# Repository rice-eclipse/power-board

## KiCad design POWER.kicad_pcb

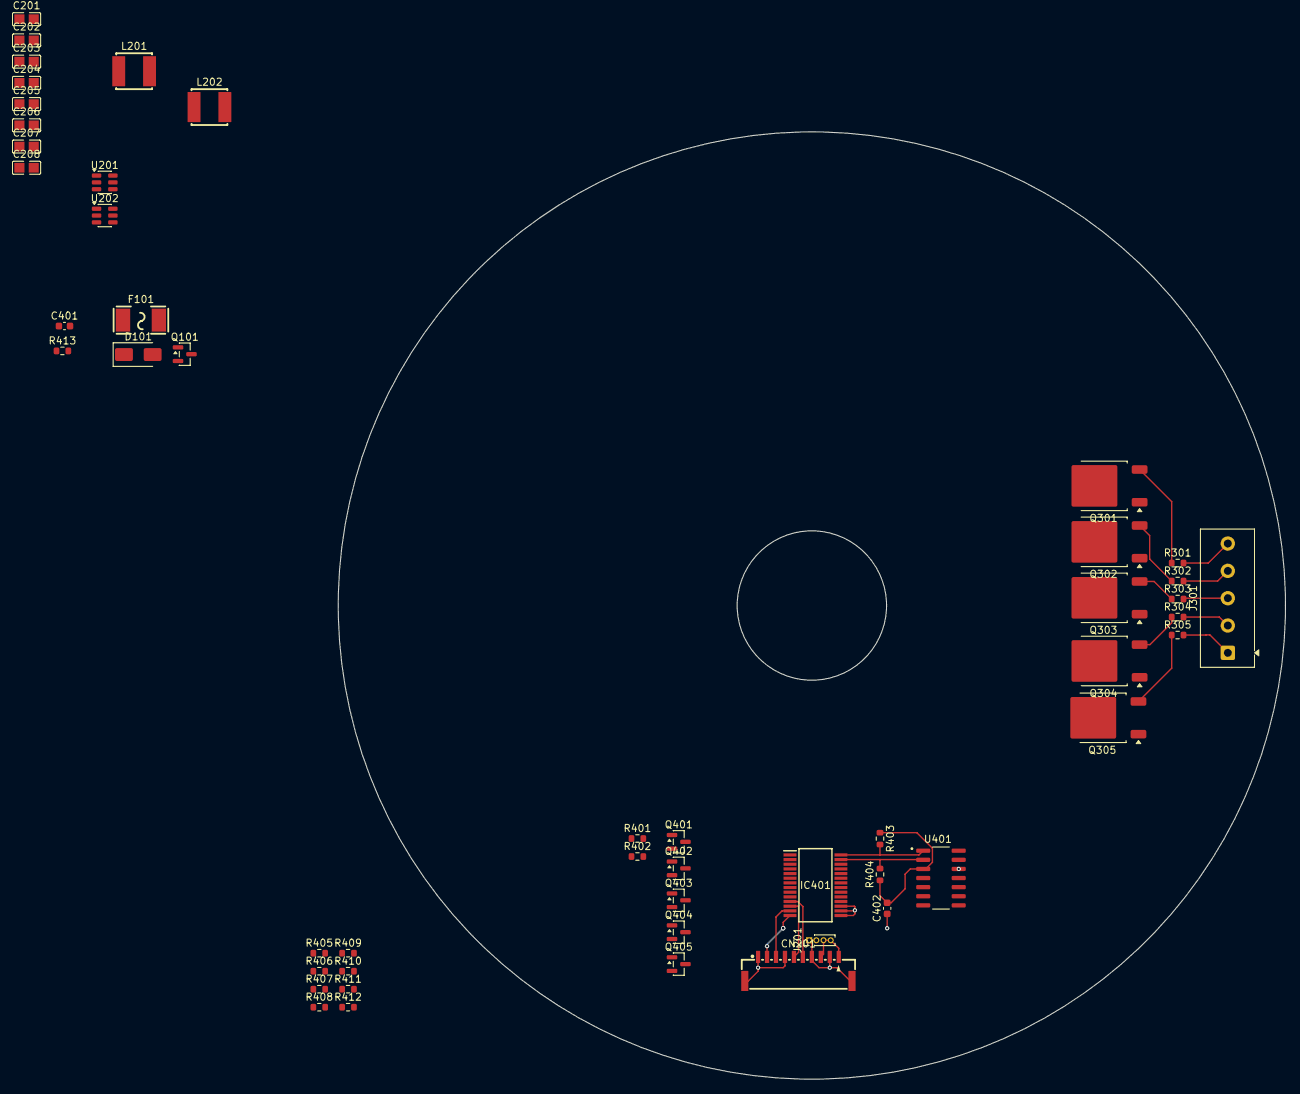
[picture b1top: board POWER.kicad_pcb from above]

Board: 4 copper layers, 132.1 x 132.1 mm, 50 parts (0 on the bottom side), 37 nets.

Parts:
C201, C204, C207, C208: 22uF; CL21A226MPQNNNE
C202, C205: 10uF; CL21A106KAYNNNE
C203, C206: 100nF; CL21B104KCFNNNE
C401, C402: 0.1 UF; C_0603_1608Metric
CN201: BM10B-GHS-TBT_LF_SN
D101: SMAJ10A; D_SMA
F101: JFC2410-2100FS
IC401: MCP23S17T-E_SS; SOP65P780X200-28N
J201: Conn_01x04_Pin; PinHeader_1x04_P1.00mm_Vertical
J301: Screw_Terminal_01x05; TerminalBlock_Phoenix_MKDS-1-5-3.81_1x05_P3.81mm_Horizontal
L201, L202: 3.9uH; FNR5040S3R9NT
Q101: AO3401A; SOT-23
Q301, Q302, Q303, Q304, Q305: AP25P06K; TO-252-2
Q401, Q402, Q403, Q404, Q405: 2N7002; SOT-23
R301, R302, R303, R304, R305, R402, R406, R408, R410, R412: 100K; R_0603_1608Metric
R401, R405, R407, R409, R411: 100; R_0603_1608Metric
R403, R404, R413: 10k; R_0603_1608Metric
U201, U202: AP63203WU; TSOT-23-6
U401: LM339ADR; SOIC127P600X175-14N

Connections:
+3V3_FC: C207.1, C208.1, C401.1, C402.2, CN201.1, CN201.3, IC401.9 (VDD), J201.3, J201.4, L202.2, R403.1, R404.1, R413.2, U202.1 (FB), U401.3 (VCC+)
+3V3_RF: C201.1, C204.1, L201.2, U201.1 (FB)
/CS_PYRO: CN201.5, IC401.11 (~CS)
/MISO: CN201.9, IC401.14 (SO)
/MOSI: CN201.8, IC401.13 (SI)
/SCLK: CN201.6, IC401.12 (SCK)
/pyro-control/ARM_1_RESISTOR: IC401.1 (GPB0), R401.1
/pyro-control/ARM_2_RESISTOR: IC401.2 (GPB1), R405.1
/pyro-control/ARM_3_RESISTOR: IC401.3 (GPB2), R407.1
/pyro-control/ARM_4_RESISTOR: IC401.4 (GPB3), R409.1
/pyro-control/ARM_5_RESISTOR: IC401.5 (GPB4), R411.1
ARM: Q301.1 (G), Q302.1 (G), Q303.1 (G), Q304.1 (G), Q305.1 (G)
GND: C201.2, C202.2, C204.2, C205.2, C207.2, C208.2, C401.2, C402.1, CN201.2, CN201.4, CN201.7, CN201.10, CN201.11, CN201.12, D101.2 (A2), IC401.10 (VSS), IC401.15 (A0), IC401.16 (A1), IC401.17 (A2), J201.1, J201.2, Q101.1 (G), Q401.2 (S), Q402.2 (S), Q403.2 (S), Q404.2 (S), Q405.2 (S), R402.1, R406.1, R408.1, R410.1, R412.1, U201.4 (GND), U202.4 (GND), U401.12 (VCC-)
unnamed: IC401.27 (GPA6), R404.2, U401.2 (OUT2)
unnamed: IC401.28 (GPA7), R403.2, U401.1 (OUT1)
unnamed: IC401.18 (~RESET), R413.1
unnamed: J301.1, R305.2
unnamed: J301.2, R304.2
unnamed: J301.3, R303.2
unnamed: J301.4, R302.2
unnamed: J301.5, R301.2
unnamed: F101.2, Q101.3 (D)
unnamed: Q301.3 (S), R301.1
unnamed: Q302.3 (S), R302.1
unnamed: Q303.3 (S), R303.1
unnamed: Q304.3 (S), R304.1
unnamed: Q305.3 (S), R305.1
unnamed: Q401.1 (G), R401.2, R402.2
unnamed: Q402.1 (G), R405.2, R406.2
unnamed: Q403.1 (G), R407.2, R408.2
unnamed: Q404.1 (G), R409.2, R410.2
unnamed: Q405.1 (G), R411.2, R412.2
unnamed: C203.2, U201.6 (BST)
unnamed: C203.1, L201.1, U201.5 (SW)
unnamed: C206.2, U202.6 (BST)
unnamed: C206.1, L202.1, U202.5 (SW)
V_BATT: C202.1, C205.1, D101.1 (A1), Q101.2 (S), Q301.2 (D), Q302.2 (D), Q303.2 (D), Q304.2 (D), Q305.2 (D), U201.2 (EN), U201.3 (IN), U202.2 (EN), U202.3 (IN)
